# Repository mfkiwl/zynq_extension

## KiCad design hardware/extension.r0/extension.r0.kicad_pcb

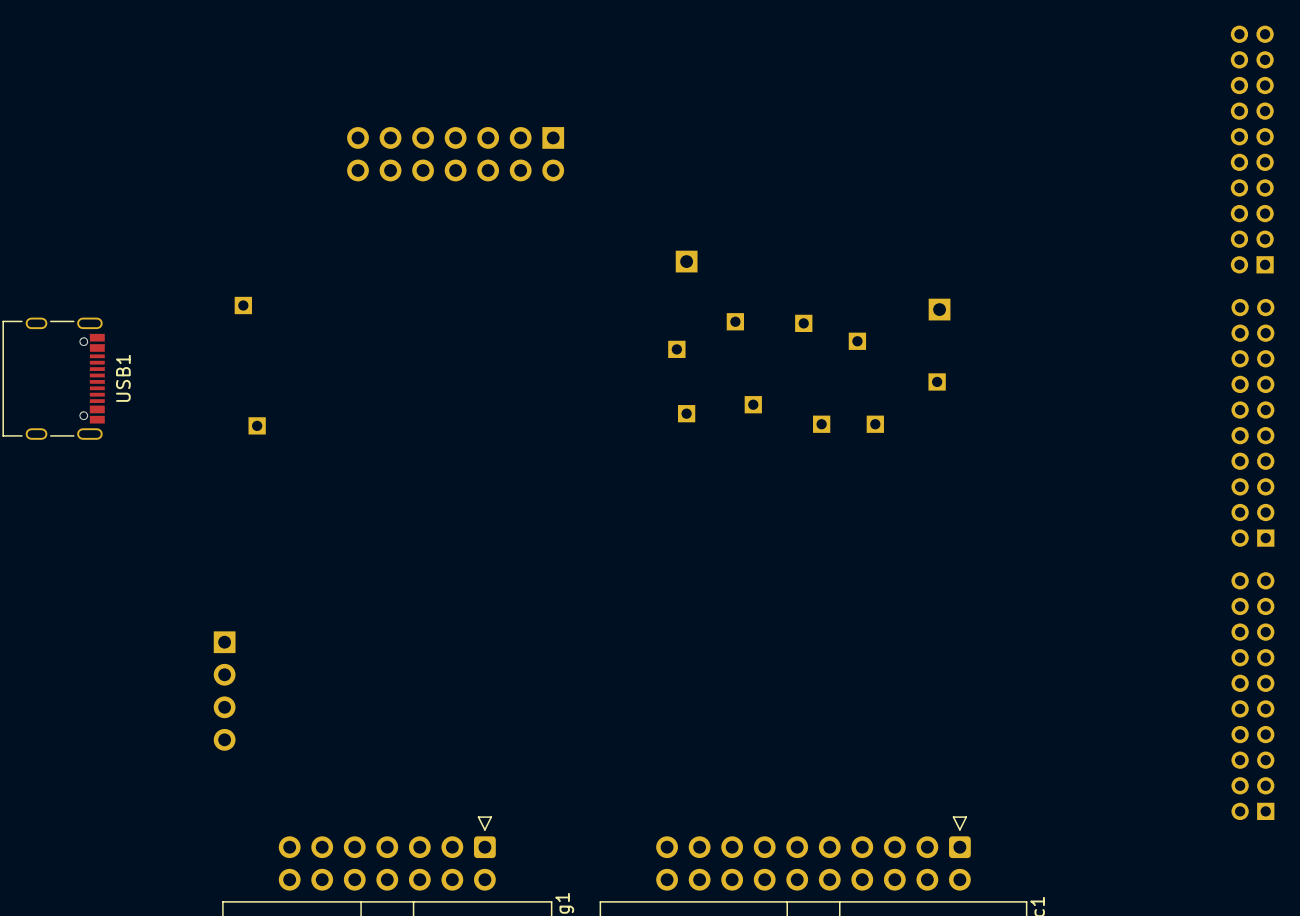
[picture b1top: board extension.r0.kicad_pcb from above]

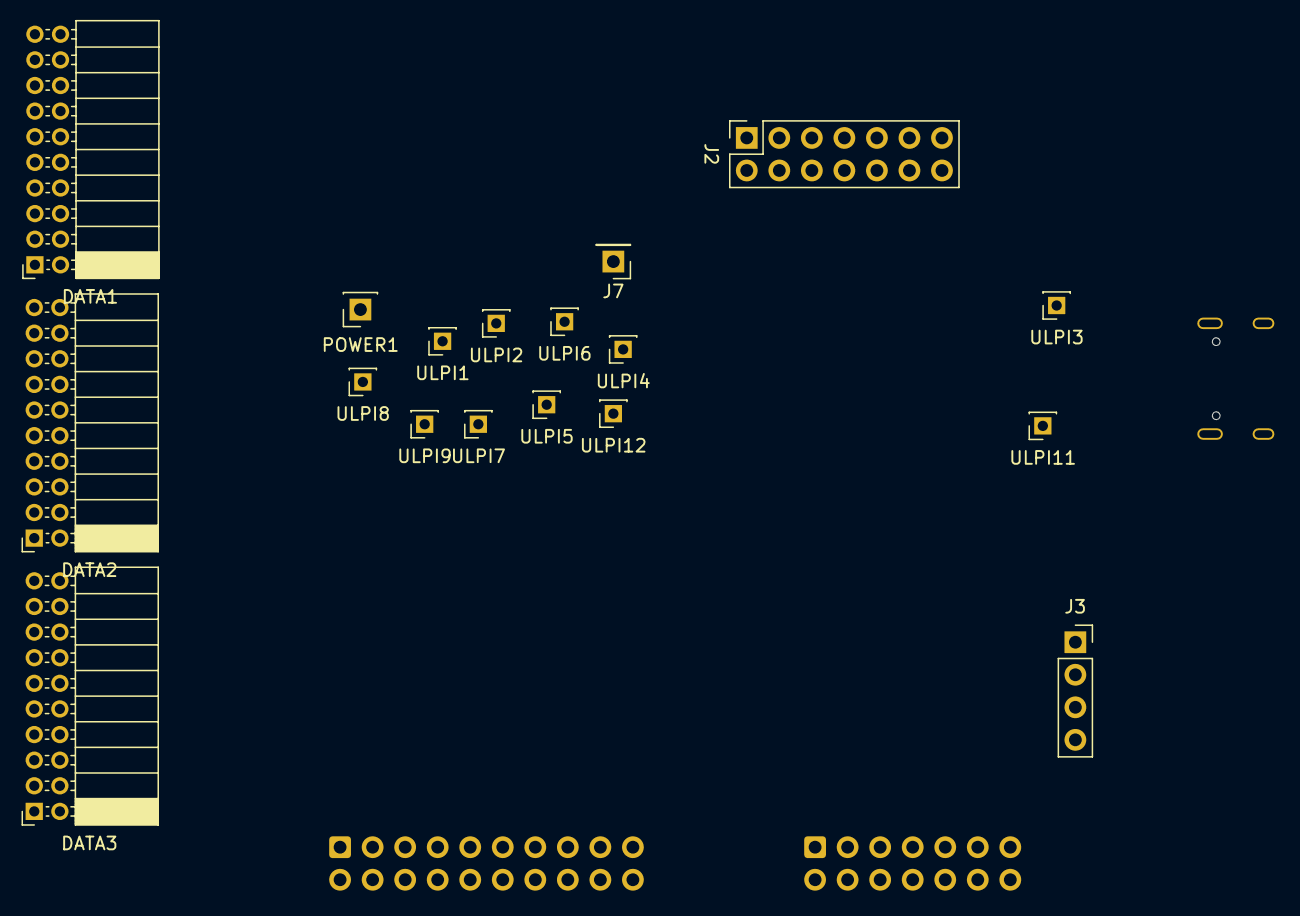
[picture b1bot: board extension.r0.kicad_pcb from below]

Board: 2 copper layers, 21 parts (18 on the bottom side), 7 nets, no tracks yet.

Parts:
DATA1, DATA2, DATA3: Conn_02x10_Odd_Even; PinSocket_2x10_P2.00mm_Horizontal
Debug1: Conn_02x07_Odd_Even; IDC-Header_2x07_P2.54mm_Horizontal
J2: JTAG; PinSocket_2x07_P2.54mm_Vertical
J3: UART; PinSocket_1x04_P2.54mm_Vertical
J7: Vdrive_I; PinHeader_1x01_P2.54mm_Vertical
Logic1: Conn_02x10_Odd_Even; IDC-Header_2x10_P2.54mm_Horizontal
POWER1: Conn_01x01; PinSocket_1x01_P2.54mm_Vertical
ULPI1, ULPI2, ULPI3, ULPI4, ULPI5, ULPI6, ULPI7, ULPI8, ULPI9, ULPI11, ULPI12: Conn_01x01; PinSocket_1x01_P2.00mm_Vertical
USB1: USB_C_Receptacle_USB2.0; USB_C_Receptacle_Palconn_UTC16-G

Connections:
/VBUS: USB1.A4, USB1.A9, USB1.B4, USB1.B9
/VCC: J2.2, J3.4
/VCC_DATA: DATA1.19, DATA1.20, DATA2.19, DATA2.20, DATA3.19, DATA3.20
/ZYNQ_: DATA1.1, DATA1.2, DATA1.3, DATA1.4, DATA2.1, DATA2.2, DATA2.3, DATA2.4, DATA2.5, DATA2.6, DATA2.7, DATA2.8, DATA2.10, DATA2.12, DATA2.13, DATA2.14, DATA2.15, DATA2.16, DATA3.1, DATA3.2, DATA3.3, DATA3.4, DATA3.5, DATA3.6, DATA3.7, DATA3.8, DATA3.10, DATA3.12, DATA3.13, DATA3.14, DATA3.15, DATA3.16
GND: DATA1.9, DATA1.17, DATA1.18, DATA2.9, DATA2.17, DATA2.18, DATA3.9, DATA3.17, DATA3.18, Debug1.4, J2.1, J2.3, J2.5, J2.7, J2.9, J2.11, J2.13, J3.1, Logic1.9, Logic1.10, Logic1.19, Logic1.20, USB1.A1, USB1.A8, USB1.A12, USB1.B1, USB1.B8, USB1.B12
unnamed: USB1.A7, USB1.B7
unnamed: USB1.A6, USB1.B6

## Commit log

2021-02-21 backup
